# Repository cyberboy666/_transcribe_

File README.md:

# \_transcribe\_

### midi to rs232 bridge - for performance control of old video mixers and switchers

- this circuit is distributed by __UNDERSCORES__ - _an open video hardware label_ : it is available to purchase - as a pcb, kit or assembled unit - at [underscores.shop](https://underscores.shop/_transcribe_/)
- the schematic for the circuit can be found [here](/hardware/schematic.pdf)
- the pcb gerber files for the lastest version can be found [here](/hardware/gerber_latest.zip)
- interactive BOM is [here](https://htmlpreview.github.io/?https://github.com/cyberboy666/_transcribe_/blob/main/hardware/bom/ibom.html)
- consider [donating](https://opencollective.com/underscores) to the underscores project to help us continue creating for the commons
## description

people in the video-art community are performing with old hardware video-mixers such as the Pansonic_WJ_AVE55 and Pansonic_WJ_MX30/50. some of these mixers have a RS232 serial port for interfacing with them digitally. this is especially useful for live performance where sequencing can assist physical actions. there are some cool examples of software specifically written to interface with these mixers (such as [Freds excel app](https://a2m2.ch/fred/wj-ave55.htm) and  [Klifs MaxPatch](https://vimeo.com/161662975) ) , but there many more programs and devices that are made to interface digitally using MIDI.

the aim of this project is to create a small utility module that can __\_transcribe\___ _MIDI_, a protocol used commonly in live&performance instruments to the specific _RS-232 video-device specification_ , to better equip these retired workstations for their new life of glamour on stage

- input USB-midi from a USB-HOST such as a computer or rpi
- input serial-midi from older midi devices (din5)
- input USB-midi for a USB-DEVICE such as a korg nanokontroller or otherwise
- output RS232-serial commands over 3.5mm jack or dsub9 socket to control panasonic video-mixers and other devices
- all these interfaces are bi-directional and so can be modified with firmware to do other useful things (eg like a USB-DEVICE -> SERIAL midi converter)

## demo video

# documentation

this project is fully _open-source hardware_ - all the files required to build it are included in this repo for free. if you have the time and/or skill you can contribute back by collaborating on / testing new designs, improving these docs, making demo videos/other creative content etc. you can also support the project financially by [donating directing](https://opencollective.com/underscores), or purchasing through the [web shop](https://underscores.shop).

depending on whether you are going fully diy or buying an assembled and tested unit, some of the following guides will be relavent to you. the flow would be:

## ordering parts

<details><summary><b>parts sourcing guide (w/ notes on pcb fabracation )</b> - start here if you are building fully from scatch or have purchased a pcb</summary>

i try to source all the parts i can from either:
- [tayda](https://www.taydaelectronics.com/) ; cheaper for common parts like resistors etc, also good for mechanical parts like switches and buttons
- [mouser](https://www.mouser.de/) ; has lots more options, speciality video ic's, can sometimes cost more (free shipping on orders over 50euros)
- other ; ocationally there will be parts which will need to be sourced elsewhere - usaully either aliexpress, ebay or amazon etc...

take a look at the [full_bom](/hardware/bom/full_bom.csv) for this project to see where i am sourcing each part from
  
## omitting parts
  
if you know exactly how you will use your _transcribe_ some parts of this circuit build can be omitted. the pcb is divided into sections that are marked on silk-screen:

- __A - micro-conntroller - centre__ : this is the brain of the circuit and is required to make it do anything. its also where USB_MIDI is received from(/sent to) usb-hosts (eg computer or raspberry pi)
- __B - rs232 serial - output(/input)__ : for sending(/receiving) serial at rs232 levels - only omit if you are not using this board for its default / intended purpose
- __C - serial midi - input(/output)__ : for receiving(/sending) midi messages over serial (usually on older hardware over din5 or 3.5mm jack) - can omit if you are only using (newer) hardware with USB-MIDI
- __D USB-midi HOST__: adds circuitry so that micro-controller can act as USB-HOST. for receiving midi messages from(/sending to) usb-devices (eg korg nanokontrol2) - can omit this if not interested in controlling from usb-devices

## import into tayda

- go to the [tayda quick order](https://www.taydaelectronics.com/quick-order/) and in bottom corner choose _add from file_
- select the file [tayda_bom.csv](./hardware/bom/tayda_bom.csv) in the BOM folder (you will have to download it first or clone this repo)
- after importing select _add to cart_
- __NOTE:__ the minimum value for resistors is 10, so you may need to modify these values to add to cart (or if they are already modified here you will need to see the  full_bom for actual part QTY) 

- OPTIONAL: it is a good idea to add some dip-ic sockets and 2.54pin headers/sockets to your tayda order if you dont have them around already
  
## import into mouser

- go to [mouser bom tool](https://nz.mouser.com/Bom/) and click _upload spreadsheet_
- select the file [mouser_bom.csv](./hardware/bom/mouser_bom.csv) in this folder (you will have to download it first or clone this repo), then _upload my spreadsheet_ and _next_
- ensure that __Mouser Part Number__ is selected in the dropdown above the first row, then _next_, _process_
- if everything looks correct can now put _add to basket_

# ordering pcbs

you can support this project by buying individual pcbs from the [shop](https://underscores.shop). if you would rather have pcbs fabricated from gerbers directly the file you need is [here](/hardware/gerber_latest.zip) 

- i get my pcbs fabricated from [jlcpcb](https://cart.jlcpcb.com/quote) - 5 is the minumum order per design
- upload the zip file with the `add gerber file` button
- the default settings are mostly fine - set the __PCB Qty__ and __PCB Color__ settings (you can check that the file looks correct with pcb veiwer)
- it may be best to combine orders with other pcbs you want to have fab'd since the shipping can cost more than the items - also orginising group buys is a good way to distribute the extra pcbs /costs 
  
i often use jlcpcb because they are reliable, cheap and give you an option of colours. remember though that the cheapest Chinese fab houses are not always the most ethical or environmently friendly - if you can afford it consider supporting local companies. 

</details>

<details><summary>a note on midi over 3.5mm trs jacks</summary>

in general newer devices send midi over usb, and older ones send serial-midi over _din5 jacks_. however some newer devices opt to send serial-midi over __3.5mm trs jacks__ (to save space on more compact designs)

_transcribe_ has (overlapping) footprints for either serial-midi over _din5_ or over __3.5mm trs__

unfortunately at the time that designers started using __3.5mm trs jacks__ for midi there was no offical standard for which pins map to midis _source_ (`midi_plus`) and _sink_ (`midi_data`) pins and different designers have mapped this differently on their instruments.

now there is an offical standard - TYPE A - which is what _transcribe_ uses: 

- t -> _sink_ (data)
- r -> _source_ (plus)
- s -> x

[minimidi.world](https://minimidi.world/) is a great resource that explains the different standards and allows you to look up the type of _serial midi over 3.5mm trs_ that your devices have - i recommend taking a look at this if you are planning on using 3.5mm trs with your _transcribe_

</details>

## assembly guide

<details><summary><b>assembly guide</b> - start here if you have purchased a diy kit</summary>

## interactive BOM for build guiding

follow this link to view the [interactive BOM](https://htmlpreview.github.io/?https://github.com/cyberboy666/_transcribe_/blob/main/hardware/bom/ibom.html)

## general solder advices

- remember to heat pad first (2-3seconds), then add solder, then continue to heat (1-2seconds)

- Checkout the web-comic [soldering is easy](https://mightyohm.com/files/soldercomic/FullSolderComic_EN.pdf) for more soldering advice

## general order of assembly

- in general while assembling i start placing resistors and capacitors first. placing 5 - 10 components at a time and then flipping the board to solder them and trim the legs etc.
- next i would do diodes, transistors and ic's - taking care that these are placed in the right direction (using a ic socket can be useful)
- finally i place the interface parts - rca jacks, power jack, pots and switches - make sure these have lots of solder on for structural stablity

## interface choice / double footprint
  
_serial-midi_ is most commonly sent over __din5__ (older hardware) J5 & J7 or __trs 3.5mm jack__ (newer hardware) J4 & J6 - footprints for both are overlayed on the pcb so you can choose which one you would like to have
  
## Usb-host shield

__IMPORTANT: A trace needs to be cut on the usb-host-shield to allow it to be powered by 5v__ – _see the diagram below_ – this is best done with a craft knife – take care not to cut any other traces accidentally.

all pins on the outer vertical lines need to be soldered to the board. In addition to this the single topmost inner pin (labeled 5v in diagram) needs to be soldered to pcb also
  
## specific assembly advice

Start by soldering the smallest parts first: resistors, diodes, capacitors and regulators - take note of the direction on the diodes - black bar on component matching black bar on footprint

Next lets do the ic’s/sockets - make sure the direction is correct! place in and fold two corner pins to hold in place, then solder all pins. you can place the ic in now too

Now lets do the micro-controller and usb-host-shield - if you want to be able to remove them from the board you will need to solder header sockets to the board first – otherwise can directly solder the header pins

for the usb-host-shield right_row I would do a 1x2 header horizontally at the top to catch that 5v pin and then 1x11 row vertically for the rest – the left_row can just be a single 1x12 vertical header

Finally place the interface parts (eg jacks and sockets) be generous with the solder here -> this is to strengthen the mechanical connections as well as making electrical ones

Leave j8 header unpopulated – this just exposes the bootloader pins so firmware can be reset in the rare case that the pro-micro gets bricked – also leave j1 header unpopulated unless you want to power from a euro-power-header
  
</details>

## firmware guide

<details><summary><b>firmware guide</b> - for editing the code & flashing it to your micro-controller</summary>
  
## flashing firmware onto the micro-controller
  
if you have got a kit from the shop the default firmware will be pre-configured - still you probably will want to follow this so you can edit the code and update the mappings.
  
### install guide
  
all _underscores_ projects with micro-controllers use [platformio](https://platformio.org/) with [visual studio code](https://code.visualstudio.com/) to edit, flash and monitor the code.
  
- first download (and unzip) the code in this repo - easiest is [as a zip](https://github.com/cyberboy666/_transcribe_/archive/refs/heads/main.zip) or you can clone using git if you are comfortable with this
- next download, install and open [visual studio code](https://code.visualstudio.com/#alt-downloads)
- now open the extension tab within vscode on left vertical menu (or press ctrl-shift-x) and search for `platformio` to install this extension

- connect the micro-controller to computer via usb, open the _transcribe_ software folder (ctrl-k ctrl-o) in vscode and find the _platformio_ commands (either in left vertical menu under _platformio_ or little tick/arrow symbols along bottom blue bar) - `PlatformIO: Upload` should flash the default code to your micro-controller

### mapping edit guide
  
this guide is just an overview to get you started. the two files that you might want to look at are: 
- [software/src/commands.h](software/src/commands.h) - where the specific serial protocol commands are defined
- [software/src/main.cpp](software/src/main.cpp) - all the code that handles receiving midi and writing serial is - including the _mapping function_
  
open the `src/main.cpp` file in vscode and fold all functions by pressing `ctrl-k, ctrl-0` - this makes reading it a bit easier:

open and take a look at the `setAVE55nanokontrolMap` method - we will first look at these lines:
  
```cpp
    else if(midiParam1 == 64){setCmd(A55_A_BUS_SOURCE_1);}
    else if(midiParam1 == 65){setCmd(A55_A_BUS_SOURCE_2);}
```
  
the first line is saying: __if the incoming midi message has `midiParam1` set to 64, then send the `A55_A_BUS_SOURCE_1` command over rs232 serial__ - since we can see from above that this line is within the conditional: `if(midiCommand == MIDICOMMAND::CC)` , then we know that `midiParam1` is refering to the cc channel. we can also see in the __commands.h__ file  that `A55_A_BUS_SOURCE_1` is set to the command from that panasonic ave55 specification that switches the a-bus source to input 1:
```cpp
  #define A55_A_BUS_SOURCE_1 "VCP:200"
```

this line is mapping a midi message on cc channel 64 to the rs232 message for ave55 that switches the input source. this is the simplest kind of mapping - a discrete BUTTON press. however there are also mappings to functions that take parameter values also. for example the `A55_A_B_MIX_LEVEL` command that wipes between the a-bus to b-bus on the mixer:
  
 ```cpp
 if(midiParam1 == 0){setCmd(A55_A_B_MIX_LEVEL, midiParam2);}
 else if(midiParam1 == 1){setCmd(A55_THRESHOLD_LUM_KEY, midiParam2);}
 else if(midiParam1 == 2){setCmd(A55_CENTER_WIPE_X, midiParam2);}
 else if(midiParam1 == 3){setCmd(A55_CENTER_WIPE_Y, midiParam2);}
```

we can see that on these mappings also the __midiParam2__ value is passed into the _setCmd_ function - this is the _cc value_ of the channel - on my controller - the position of the slider that is sending on cc channel 0. the rs232 command for this function also takes a varible input to set position of the mix:
```cpp
#define A55_A_B_MIX_LEVEL "VMM:179~0"
```
where the `~0` is a placeholder that is replaced with the hex-converted value of `midiParam2`. there are other ways to map midi notes to rs232 commands. there are more 'advanced' mapping functions in the code for this - for example:
```cpp
else if(midiParam1 == 35){setCmdParamRandom(A55_A_B_MIX_LEVEL);}
```
takes a button press and converts it to a random mix level. another useful mapping is taking continuous inputn (eg slider on midi controller)  and convert this to a STEP of different discrete commands - for example:
```cpp
else if(midiParam1 == 17){setCmdStepAVE55(A55_A_BUS_MOSAIC_OFF, midiParam2, 76, 6);}
else if(midiParam1 == 18){setCmdStepAVE55(A55_A_BUS_PAINT_OFF, midiParam2, 82, 6);}
```
these mappings STEP between sending 6 different rs232 commands on a single slider - so you can set all the mosaic/paint effect levels in one turn. another useful 'advanced' mapping function is the SWITCH:
  
```cpp
else if(midiParam1 == 50){setCmdSwitch(MX50_A_BUS_EFFECT_ON, MX50_A_BUS_EFFECT_OFF, 3);}
```

this will SWITCH between sending the _on_ and _off_ commands when the same midi command is send (the third parameter input `3` is a unique index reference to store the on/off state in memory between messages)
  
these are just some examples of the ways that code can be used to perform these mappings. if you are interested can see more in the code directly or write your own mapping functions!

</details>
  
## operating guide
  
<details><summary><b>operating guide</b> - start here if you have purchased an assembled unit</summary>

</details>

### more info

<details><summary><b>how the circuit works</b></summary>
  
[coming soon]
                                                                                                                             
</details>

<details><summary><b>contributing guide</b></summary>
  
if you would like to contribute back to these projects in some way but dont know how the best thing (for now) would be to reach out to me directly ( tim@cyberboy666.com or @cyberboy666 on scanlines forum) - i will be happy to help
  
</details>

## credits & more info

This circuit is distributed through UNDERSCORES – open video hardware label – visit [underscores.shop](https://underscores.shop) for more info

The pcb was designed using KICAD

Everything from gerbers, cad files, panels and documentation is freely available online and distributed under CC-BY-SA / open-source licenses – help us contribute to the commons !

Ask any questions or start discussions related to this project on the [scanlines.xyz](https://scanlines.xyz) forum – an online community space dedicated to diy av / electronic media art

You can contact me directly at tim (at) cyberboy666 (dot) com 
Please get in touch if you are interested in hosting a workshop !

Thanks to Gilbert Sinnott for helping with initial experiments. to Bastien Lavaud for circuit advice, always. To Ben Caldwell for project advice. To everyone who has or will contribute ♥♥♥

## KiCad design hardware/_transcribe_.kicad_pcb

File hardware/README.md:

# _transcribe_ hardware

this is the hardware section of _transcribe_ - a project created to control panasonic video_mixers with midi.

# BOM

Reference | Qty | Value | source | source-id | section
--- | --- | --- | --- | --- | ---
? | 1|  _transcribe_ pcb | me? or a fab-house | ...  | all
C1 | 1 | 100uf | tayda | [A-1063](https://www.taydaelectronics.com/catalogsearch/result/?q=A-1063) | A 
C2, C3, C4, C5 | 4 | 0.1uf | tayda | [A-4008](https://www.taydaelectronics.com/catalogsearch/result/?q=A-4008) | B
D1, D2 | 2 | 1N4148 | tayda | [A-157](https://www.taydaelectronics.com/catalogsearch/result/?q=A-157) | C
J1 | 1 | europower header (optional) | tayda | [A-2956](https://www.taydaelectronics.com/catalogsearch/result/?q=A-2956) | -
J2, J4, J6 | 3 | AudioJackTSR | tayda | [A-853](https://www.taydaelectronics.com/catalogsearch/result/?q=A-853) | B , C
J3 | 1 | DSUB9 | tayda | [A-300](https://www.taydaelectronics.com/catalogsearch/result/?q=A-300) or [A-301](https://www.taydaelectronics.com/catalogsearch/result/?q=A-301) | B , C
J5, J7 | 2 | DIN-5 | tayda | [A-1010](https://www.taydaelectronics.com/catalogsearch/result/?q=A-1010) | B , C
R1, R2, R3 | 3 |  220 | tayda | [A-3755](https://www.taydaelectronics.com/catalogsearch/result/?q=A-3755)  | C
R4 | 1 | 10k | tayda | [A-2275](https://www.taydaelectronics.com/catalogsearch/result/?q=A-2275)  | C
U1 | 1 | ProMicro5v | [ali](https://www.aliexpress.com/item/1348800135.html) [amazon](https://www.amazon.com/OSOYOO-ATmega32U4-arduino-Leonardo-ATmega328/dp/B012FOV17O/), [sparkfun](https://www.sparkfun.com/products/12640) | - | A
U2 | 1 | MAX232n | tayda | [A-034](https://www.taydaelectronics.com/catalogsearch/result/?q=A-034) | B
U3 | 1 | 6N137 | tayda | [A-871](https://www.taydaelectronics.com/catalogsearch/result/?q=A-871) | C
U4 | 1 | 4069 |  tayda | [A-882](https://www.taydaelectronics.com/catalogsearch/result/?q=A-882) | C
U5 | 1 | usbHostMini | [ali](https://www.aliexpress.com/item/32842815739.html) [amazon](https://www.amazon.com/HiLetgo-Development-Compatible-Interface-Arduino/dp/B01EWW9R1E/) | - | D
U6 | 1 | 78L33 | tayda | [A-492](https://www.taydaelectronics.com/catalogsearch/result/?q=A-492) | D

<details><summary>CORRECTION FOR CIRCUIT V0.2 AND LOWER</summary>

if you have circuit revision 0.2 or lower then there is a mistake on the footprint of the dsub9 connector sorry (serial from the 3.5mm jack to ave55 works fine) follow the following steps to get serial from the dsub9 header on these boards:

- solder the DSUB9_HEADER onto the bottom of the board
- from here pins 2 and 3 need to be swapped
- cut both traces going to dsub (the traces going between and around c2)
- wire the other ends pin13 and pin14 of u2 to the pins on dsub. u2_pin13 to dusb_pion3 and u2_pin14 to dsub_pin2 
- finally due to another error on the board IF you have placed the 3.5mm jack at J2 THEN you must have a stereo cable plugged into this to use the DSUB9 output (otherwise signal is grounded)

</details>

## potential additional parts to add : 

## assemble guide :

- i soldered the resistors, capicitors, diodes and regulator first, then the ics(/sockets) and pin headers, then the jacks
- i used pin sockets to attach the pro-micro and usb host to board in detatchable way (helpful for debugging) but this is up to you

blah blah blah

IF USING USB_HOST_MIDI YOU __MUST CUT A TRACE__ ON THE BOARD ! heres how - ...

the trace you need to cut is going into the resistor labelled 2.2k in the top corner near the usb socket

# explaining the sections of _transcribe_

 _transcribe_ is based around an arduino micro controller. included in this circuit are a number of different ways to input midi and output serial. you can choose which sections to populate based on your personal requirements.

## A - micro-conntroller - centre

this is the brain of the circuit and is __required__ to make it do anything. i am using a sparkfun pro-micro 5v, which uses micro-usb as power. (it is likely this circuit will also work with an arduino nano - which will require a seperate version of the pcb - but watch this space)

## B - rs232 serial - output(/input)

panasonic video mixers (and other older devices) use a different serial standard (RS232) to micro-controllers (ttl). in this section serial commands from the uC are level-shifted to be recongised by these devices. _only obmit this section if you are not interested in controlling old (rs232) gear_. the data is exposed on a 3.5mm TRS (stereo) jack; tip - input, ring - output, sleave - ground.

NOTE - although not used by the default firmware, the hardware also allows rs232 serial input, so this porject could be modified to also control something _from_ old gear

## C - serial midi - input(/output)

the uC (in A) can act as a USB midi _device_. this means it can be controlled by a USB midi _host_ (such as a computer running abeton, or a raspberry pi). this section includes the additional circuity to also control it with serial-midi (often seen on older instruments with din5 type plugs)

NOTE - although din5 plugs are often used for connecting old gear with serial midi, these sockets can be bulky and sometimes difficult to find. for this reason newer gear supporting serial-midi often use TRS jacks - leaving the standard-conversion to cables. i would use 3.5mm TRS (stereo) also for midi in and out, with tip - midi data (din-pin4), ring - midi plus (din-pin5), sleave - unconnected (or include a switch to swap tip/ring...)

NOTE - although not used by the default firmware, the hardware also allows serial-midi output, so this project could be modified to also output serial midi

_obmit this section if you are not interested in interfacing with 'old style' serial midi_

## D USB-midi HOST

the uC (in A) can act as a USB midi _device_. this means it can be controlled by a USB midi _host_ (such as a computer running abeton, or a raspberry pi). this section includes additional circuitry to allow the uC to also act as a USB midi __HOST__. this means it can be controlled by a USB midi _device_ such as a korg nanokontroller (or many other external usb-midi controllers/ gear). _obmit this section if you are not interested in controlling from a usb-midi device_

# section summary

## video-mixer controlling options:

- control rs232-mixer with usb-midi from host : A + B
- control rs232-mixer with serial-midi : A + B + C
- control rs232-mixer with usb-midi from device : A + B + D

## some bonus converting options:

- convert usb-midi controller to serial midi : A + C + D
- convert rs232 commands to serial-midi : A + B + C
- use a ps3 controller to send serial-midi : A + C + D

## build notes for v0_5

- decide on what sections you want to build (ie need to have A, probably you want to send out serial so also add B. do you want usb-midi ? then add D, do you want serial midi in/out ? then add C etc)
- also decide what kind of serial midi ins/out jack you want - old style din5 or new 3.5mm jack ?
- i started by placing and soldering the caps and resistors, then diodes and regulator (check orientation!)
- i like to solder in pin sockets for the pro-micro and usb-header part so they can be removed if i upgrage the circuit design - this is up to you -> will need to solder in the pins onto the pro-micro and usb-host shield if not already done. note the extra pin needed on host and the trace that needs to be cut!
- if using pin sockets do this next - when cutting the sockets to fit aim your wire cutters exactly on the adjacent socket (one more) than you need - this is to ensure the pin part doesnt fall out of the socket you need when cutting. you may need to bend u6 down abit to fit socket in
- now place the j9 pins (and two jumpers setting the serial pins on din9) and the ic/ic_sockets
- finally can solder on the interface parts - midi ins and outs, din9 and 3.5mm jacks
- note dont need to solder anything on for u5 pins - this is just exposing pins on the pro-micro so it can be reflashed incase of critical error flashing - dont need to place the euroheader either - this is just incase you want to give 5v from an existing europower rail (take care of orientation of the header if doing this)

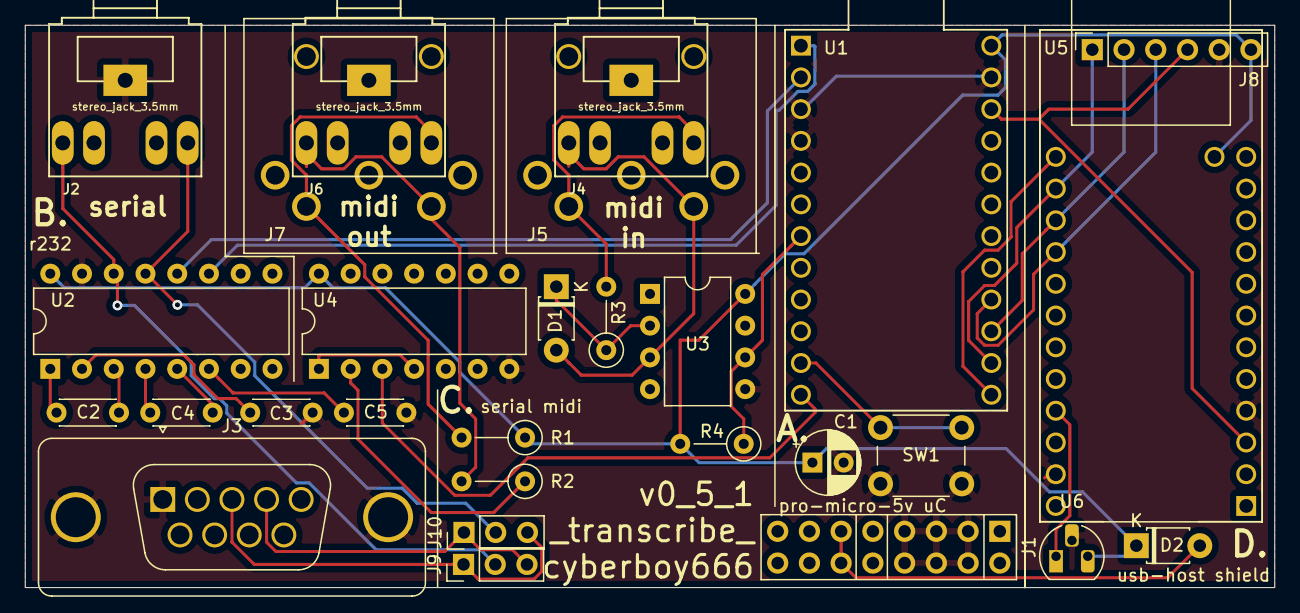
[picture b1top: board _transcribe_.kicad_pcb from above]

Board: 2 copper layers, 100.0 x 45.0 mm, 28 parts (0 on the bottom side), 31 nets.

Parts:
C1: 100uf; CP_Radial_D5.0mm_P2.50mm
C2, C3, C4, C5: 0.1u; C_Disc_D4.3mm_W1.9mm_P5.00mm
D1, D2: 1N4148; D_T-1_P5.08mm_Horizontal
J1: europower; PinHeader_2x08_P2.54_Euro
J2, J4, J6: stereo_jack_3.5mm; horizontal_3.5mm_stereo_TRS_jack_A-853
J3: dsub9_socket; tht_DSUB-9_Vertical_Tayda
J5, J7: din5; horizontal_din5-A1010
J8: bootloader; PinSocket_1x06_P2.54mm_Vertical
J9, J10: jumper; PinHeader_1x03_P2.54mm_Vertical
R1, R2, R3: 220; R_Axial_DIN0207_L6.3mm_D2.5mm_P5.08mm_Vertical
R4: 10k; R_Axial_DIN0207_L6.3mm_D2.5mm_P5.08mm_Vertical
SW1: SW_Push_Dual; SW_PUSH_6mm_H7.3mm
U1: ProMicro
U2: MAX232; DIP-16_W7.62mm
U3: 6N137; DIP-8_W7.62mm
U4: CD4069; DIP-14_W7.62mm
U5: usbHostMini; usbHostMidi
U6: 78L33; TO-92_HandSolder

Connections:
3.3v: U5.21, U6.1
+5V: C1.1, D2.1, J8.6, R1.1, R4.2, U1.24, U2.16, U3.8, U4.14, U5.25, U6.3
ALT_SERIAL_IN: U1.2, U2.12
ALT_SERIAL_OUT: U1.1, U2.11
GND: C1.2, C3.1, C5.1, J1.3, J1.4, J1.5, J1.6, J1.7, J1.8, J2.S, J3.0, J3.5, J8.5, SW1.1, U1.3, U1.4, U1.23, U2.15, U3.5, U4.7, U5.4, U5.23, U6.2
MIDI_IN_DATA: D1.2, J4.T, J5.5, U3.3
MIDI_IN_PLUS: J4.R, J5.4, R3.2
MIDI_OUT_DATA: J6.T, J7.5, R2.2
MIDI_OUT_PLUS: J6.R, J7.4, R1.2
MIDI_SERIAL_IN: R4.1, U1.7, U3.6
MIDI_SERIAL_OUT: U1.12, U4.3
MISO_HOST: J8.2, U1.15, U5.15
MOSI_HOST: J8.1, U1.14, U5.14
unnamed: C2.1, U2.1
unnamed: C2.2, U2.3
unnamed: C3.2, U2.2
unnamed: C4.1, U2.4
unnamed: C4.2, U2.5
unnamed: C5.2, U2.6
unnamed: D1.1, R3.1, U3.2
unnamed: D2.2, J1.11, J1.12
unnamed: J3.2, J9.3, J10.1
unnamed: J3.3, J9.1, J10.3
unnamed: R2.1, U4.2
unnamed: SW1.2, U1.11
unnamed: U4.1, U4.4
RST_HOST: J8.4, U1.22, U5.3
RS_SERIAL_IN: J2.R, J10.2, U2.13
RS_SERIAL_OUT: J2.T, J9.2, U2.14
SKC_HOST: J8.3, U1.16, U5.16
SS_HOST: U1.13, U5.13

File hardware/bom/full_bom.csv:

sku,qty,ref,val,vendor
A-1063,1,C1 ,100uf,tayda
A-4008,4,C2 C3 C4 C5 ,0.1u,tayda
A-157,2,D1 D2 ,1N4148,tayda
A-2956,1,J1 ,europower,tayda
A-300,1,J3 ,dsub9_socket,tayda
A-853,3,J2 J4 J6 ,stereo_jack_3.5mm,tayda
A-1010,2,J5 J7 ,din5,tayda
-,1,J8 ,bootloader
A-1324,2,J9 J10 ,jumper,tayda
A-2246,3,R1 R2 R3 ,220,tayda
A-2203,1,R4 ,10k,tayda
A-5129,1,SW1 ,SW_Push_Dual,tayda
-,1,U1 ,ProMicro
A-034,1,U2 ,MAX232,tayda
A-871,1,U3 ,6N137,tayda
A-882,1,U4 ,CD4069,tayda
-,1,U5 ,usbHostMini
A-492,1,U6 ,78L33,tayda

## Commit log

2019-12-25 experimenting with structure
2019-12-31 a mvp example working
2020-01-02 more tinkering
2020-01-05 a slider is also working
2020-01-05 link to power cap
2020-01-07 got 2input contrl working
2020-01-10 rehaulled the whole structure to be more memory efficient
2020-01-10 support midi host and device
2020-01-13 working on serial midi input
2020-01-13 restructured project files
2020-01-14 works with and without usb-device connected now
2020-01-17 added some pics from mixer manuals
2020-01-17 update footprints, schematic and started pcb
2020-01-17 chipping away at pcb layout
2020-01-19 refactering and experimenting
2020-03-28 refactored a fair bit
    moved to platformio
2020-03-29 blah
2020-03-29 small pcb fixes
2020-04-10 fixed some bugs
2020-09-21 refactored the code and updated circuit
2020-09-21 added notes around command syntax
2020-10-26 Update README.md
    Changed the amounts of audio jacks and 1N4148. Corrected the links and article numbers to smaller 10kohm and 200 ohm resistors.
2021-07-14 revised circuit v0.4
2021-10-17 update a little
2022-01-11 folder refactor
2022-02-22 Rename README.md to README_old.md
2022-02-22 update code and circuit revision
2022-02-22 renamed kicad files
2022-02-28 update bom
2022-04-27 add booklet
2022-11-27 uncomment the code
2023-02-08 add better logging for usb device
2024-04-24 writing some extra functions for reading and writing to serial/midi
2024-05-07 BUG FIX - update AltSoftSerial to define correct pins
2024-05-19 update gitattributes

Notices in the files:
README.md:
Everything from gerbers, cad files, panels and documentation is freely available online and distributed under CC-BY-SA / open-source licenses – help us contribute to the commons !
hardware/_transcribe_.kicad_pcb:
CC-BY-SA
